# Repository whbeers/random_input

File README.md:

# Random Input Fuzz Effect

This is a re-creation of the original Dallas Arbiter Fuzz Face effect circuit, continuing my attempts to design guitar effects using [KiCAD](https://www.kicad.org/).

The resulting design is a product of breadboarding and experimentation after an initial build of the original circuit. It emphasizes the ability to easily fine-tune the bias of each transistor to obtain a pleasant sound from a variety of NPN transistors (germanium or silicon). Besides this emphasis, it remains true to the original.

The board is built on the ["Noise Floor"](https://github.com/whbeers/noise_floor) pedal platform, which provides basic power protection, audio IO, and a footswitch with LED indicator.

[Schematic PDF](schematics/random_input-latest.pdf)

Instructions for biasing transistors (using the incorporated trimpots) are provided in the schematic. (This was the approach that worked for me, after a few hours of research. I'm by no means an expert and would welcome feedback.)

## Credit
The basic schematic I worked from is widely available on the internet. At the same time my research drew on analyses from far-greater experts than myself, as well as published circuit diagrams. Most notably:
 - [CODA Effects' circuit analysis](https://www.coda-effects.com/p/circuit-analysis-fuzz-face.html)
 - [RG Keen's analysis](http://www.geofex.com/article_folders/fuzzface/fffram.htm)
 - [PedalPCB Twin Face](https://www.pedalpcb.com/product/twinface/)

Thanks as always to the folks on the [freestompboxes.org](https://www.freestompboxes.org/) forum for feedback and suggestions.

Potentiometer 3D model courtesy [Vasily Kashirin](https://grabcad.com/vasily.kashirin-1).

*I am not affiliated with any of the brands, sites, or products named in this overview.*

## Versioning

My pcb designs utilize the following versioning scheme (I'll add to this as I produce more revisions):
 - v0.0XX: A candidate design that has not yet been produced and tested.
 - v0.XX: A design that has been produced, tested, and any initial errors addressed.

## Name
*The name "Random Input" is a reflection of the nature of the effect (a very basic fuzz) and security nerdery (fuzzing software using random input being a primitive technique to surface errors).*

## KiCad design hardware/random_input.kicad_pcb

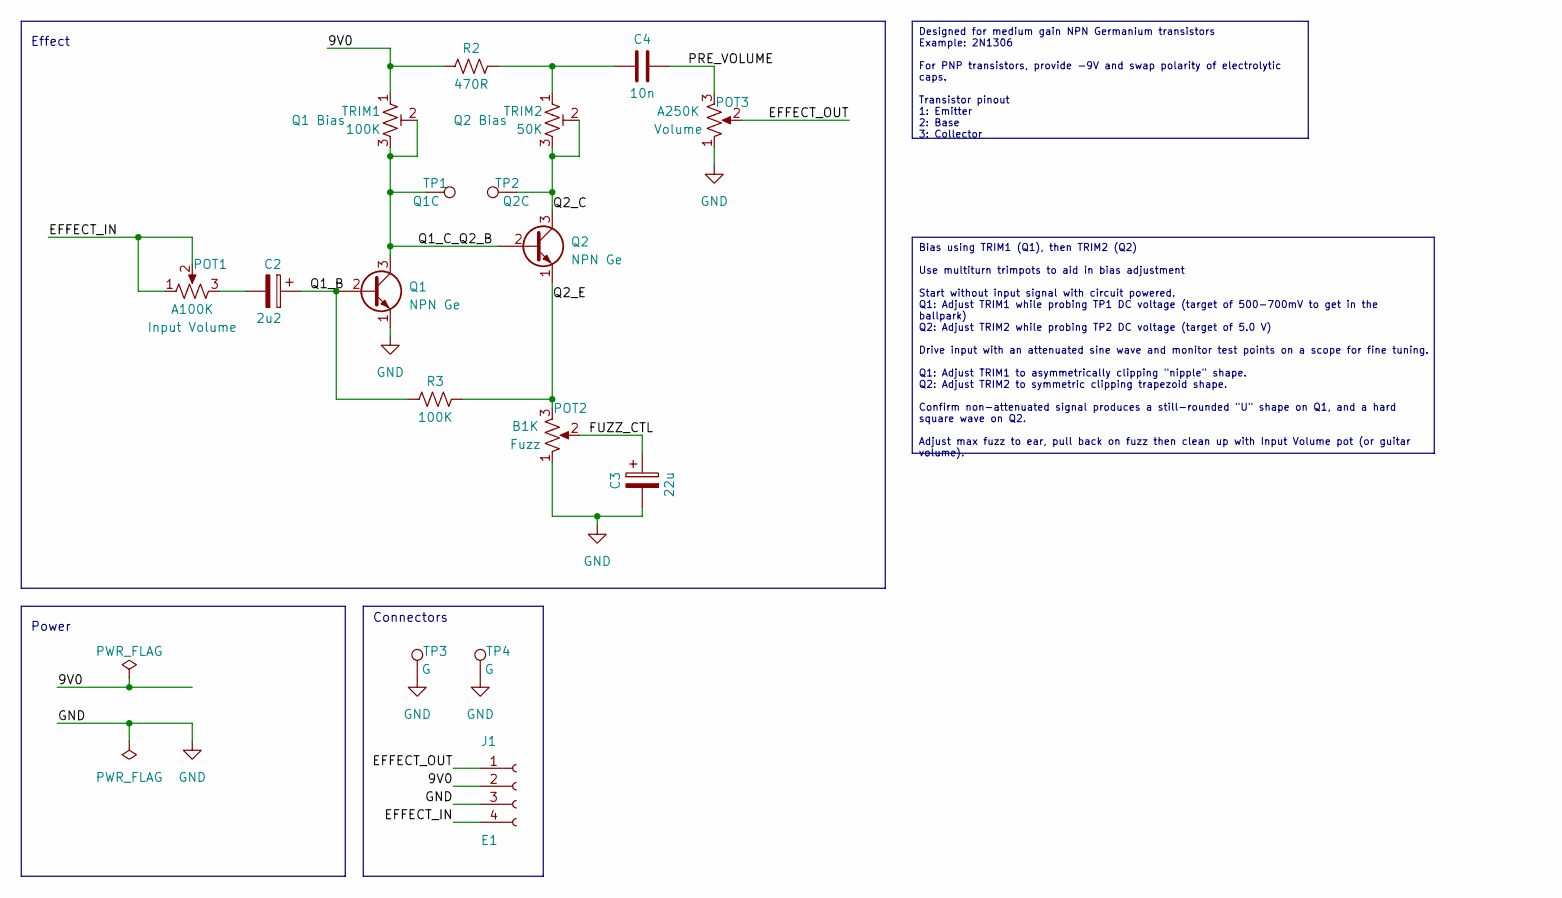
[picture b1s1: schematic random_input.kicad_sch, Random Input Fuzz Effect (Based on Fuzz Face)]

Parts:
C2: 2u2; CP_Radial_D4.0mm_P1.50mm
C3: 22u; CP_Radial_D4.0mm_P1.50mm
C4: 10n; C_Rect_L7.0mm_W2.5mm_P5.00mm
J1: E1; Molex_PicoBlade_53047-0410_1x04_P1.25mm_Vertical_with_3D_Mo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
POT1: A100K; Potentiometer_Single_3_Horizontal
POT2: B1K; Potentiometer_Single_3_Horizontal
POT3: A250K; Potentiometer_Single_3_Horizontal
Q1, Q2: NPN Ge; TO-5-3
R2: 470R; R_Axial_DIN0207_L6.3mm_D2.5mm_P7.62mm_Horizontal
R3: 100K; R_Axial_DIN0207_L6.3mm_D2.5mm_P7.62mm_Horizontal
TP1: Q1C; TestPoint_THTPad_2.5x2.5mm_Drill1.2mm
TP2: Q2C; TestPoint_THTPad_2.5x2.5mm_Drill1.2mm
TP3, TP4: G; TestPoint_THTPad_2.5x2.5mm_Drill1.2mm
TRIM1: 100K; Potentiometer_Bourns_3296W_Vertical
TRIM2: 50K; Potentiometer_Bourns_3296W_Vertical

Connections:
/9V0: J1.2, R2.1, TRIM1.1
/EFFECT_IN: J1.4, POT1.1, POT1.2
/EFFECT_OUT: J1.1, POT3.2
/FUZZ_CTL: C3.1, POT2.2
/PRE_VOLUME: C4.2, POT3.3
/Q1_B: C2.1, Q1.2 (B), R3.1
/Q1_C_Q2_B: Q1.3 (C), Q2.2 (B), TP1.1, TRIM1.2, TRIM1.3
/Q2_C: Q2.3 (C), TP2.1, TRIM2.2, TRIM2.3
/Q2_E: POT2.3, Q2.1 (E), R3.2
GND: C3.2, J1.3, POT2.1, POT3.1, Q1.1 (E), TP3.1, TP4.1
unnamed: C2.2, POT1.3
unnamed: C4.1, R2.2, TRIM2.1

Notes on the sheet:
Designed for medium gain NPN Germanium transistors Example: 2N1306 For PNP transistors, provide -9V and swap polarity of electrolytic caps. Transistor pinout 1: Emitter 2: Base 3: Collector
Bias using TRIM1 (Q1), then TRIM2 (Q2) Use multiturn trimpots to aid in bias adjustment Start without input signal with circuit powered. Q1: Adjust TRIM1 while probing TP1 DC voltage (target of 500-700mV to get in the ballpark) Q2: Adjust TRIM2 while probing TP2 DC voltage (target of 5.0 V) Drive i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
Effect
Power
Connectors

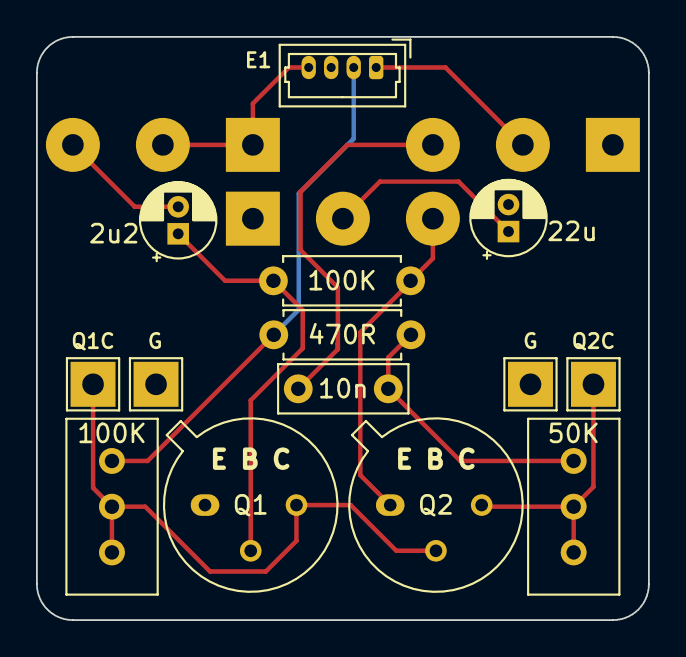
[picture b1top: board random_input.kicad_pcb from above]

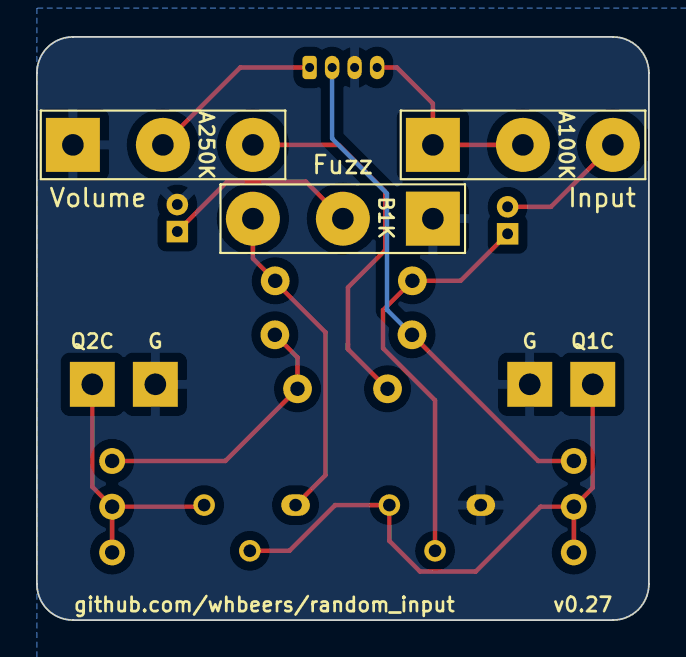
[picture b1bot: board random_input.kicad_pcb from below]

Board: 2 copper layers, 34.0 x 32.4 mm, 17 parts (3 on the bottom side), 12 nets.

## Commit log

2023-02-22 Update README.md
    fix schematic link and bullet list
2023-02-22 Update README.md
    Add versioning notes
2023-02-22 mostly cosmetic updates
    - add copper finish
    - move revision and web reference to a global variable
    - minor text updates
2023-02-24 Change to CC0 license
2023-02-28 Address issues found in v0.01 hardware
    - Move all potentiometers to back copper layer (they were reversed)
    - cosmetic/usability updates
    - adjust value of Q2 trimpot to allow correct biasing
    - swap FS and FS_G wires
2023-03-01 Updates for v0.2:
    - Switch from wire connectors to molex picoblade connectors
    - Increase size / ergonomics of bias testing pads to suit more probe types
    - Various cosmetic fixes
2023-03-02 update gitignore to include library and symbol tables
2023-03-02 add symbol table
2023-03-02 change to relative path for symbol library
2023-03-03 Offload DC protection to "noise floor" utility PCB
    - much rerouting but otherwise functionally the same
2023-03-03 rename schematic file with version number
2023-03-03 bump version number on schematic, oops
2023-03-03 Drop to a single connector to simplify, bump rev to v0.26
2023-03-04 Some updates based on feedback from freestompboxes.org folks:
    - Add back thermal reliefs on ground pads
    - Add 3D models for various parts (courtesy of Vasily Kashirin - https://grabcad.com/vasily.kashirin-1/models?page=1)
2023-03-04 fix a couple DRCs
2023-03-05 add script to generate schematic, saving time at release. also embed an SVG schematic in README.
2023-03-05 remove version note from README
2023-03-05 oops
2023-03-05 add script to export gerbers and drill files
2023-03-10 update schematic plotting script to create the directory if it doesn't exist
2023-03-10 generate new schematic (although nothing should have updated)
2023-03-13 Update to latest stable kicad version:
    - fixed issue rendering certain 3d models in color
    - had to fix some text rendering changes
2023-03-17 add disclaimer
2023-03-27 make readme consistent with others
